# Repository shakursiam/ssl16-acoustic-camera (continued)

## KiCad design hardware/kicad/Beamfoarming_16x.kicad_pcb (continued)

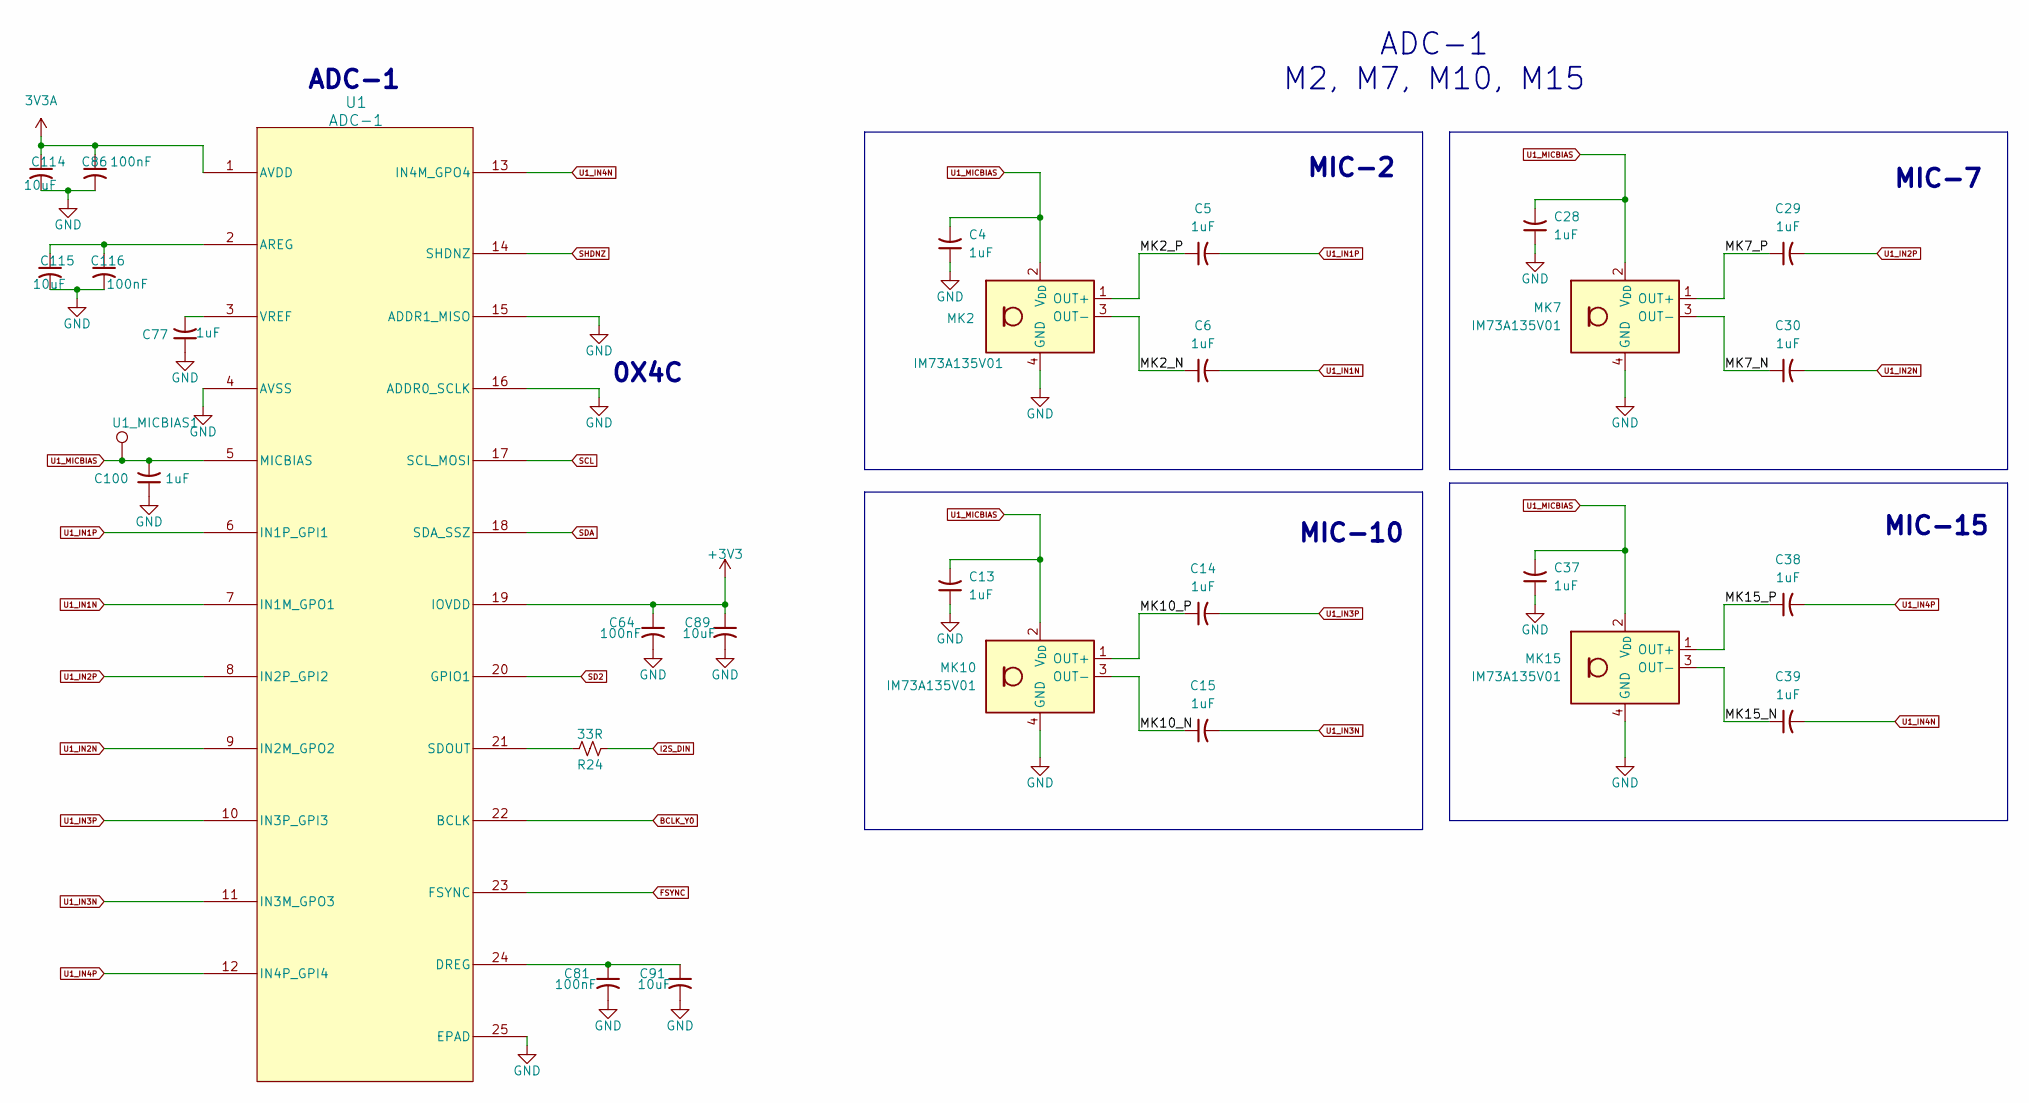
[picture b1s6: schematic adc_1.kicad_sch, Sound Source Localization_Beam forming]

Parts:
C4, C5, C6, C13, C14, C15, C28, C29, C30, C37, C38, C39, C77, C100: 1uF; C_0402_1005Metric
C64, C81, C86, C116: 100nF; C_0402_1005Metric
C89, C91, C114, C115: 10uF; C_0805_2012Metric_Pad1.18x1.45mm_HandSolder
MK2, MK7, MK10, MK15: IM73A135V01; Infineon_PG-LLGA-5-2
R24: 33R; R_0402_1005Metric
U1: ADC-1; RTW24_4P15X4P15_TEX
U1_MICBIAS1: TestPoint; TestPoint_Pad_D1.5mm

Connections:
3V3A: C86.1, C114.1, U1.1 (AVDD); also elsewhere on the board
+3V3: C64.1, C89.1, U1.19 (IOVDD); also elsewhere on the board
/ADC_1/MK2_N: C6.1, MK2.3 (OUT-)
/ADC_1/MK2_P: C5.1, MK2.1 (OUT+)
/ADC_1/MK7_N: C30.1, MK7.3 (OUT-)
/ADC_1/MK7_P: C29.1, MK7.1 (OUT+)
/ADC_1/MK10_N: C15.1, MK10.3 (OUT-)
/ADC_1/MK10_P: C14.1, MK10.1 (OUT+)
/ADC_1/MK15_N: C39.1, MK15.3 (OUT-)
/ADC_1/MK15_P: C38.1, MK15.1 (OUT+)
BCLK_Y0: U1.22 (BCLK); also elsewhere on the board
FSYNC: U1.23 (FSYNC); also elsewhere on the board
GND: C4.1, C13.1, C28.1, C37.1, C64.2, C77.1, C81.2, C86.2, C89.2, C91.2, C100.1, C114.2, C115.2, C116.2, MK2.4 (GND), MK2.5 (GND), MK7.4 (GND), MK7.5 (GND), MK10.4 (GND), MK10.5 (GND), MK15.4 (GND), MK15.5 (GND), U1.4 (AVSS), U1.15 (ADDR1_MISO), U1.16 (ADDR0_SCLK), U1.25 (EPAD); also elsewhere on the board
I2S_DIN: R24.1; also elsewhere on the board
unnamed: C115.1, C116.1, U1.2 (AREG)
unnamed: C81.1, C91.1, U1.24 (DREG)
unnamed: R24.2, U1.21 (SDOUT)
unnamed: C77.2, U1.3 (VREF)
SCL: U1.17 (SCL_MOSI); also elsewhere on the board
SD2: U1.20 (GPIO1); also elsewhere on the board
SDA: U1.18 (SDA_SSZ); also elsewhere on the board
SHDNZ: U1.14 (SHDNZ); also elsewhere on the board
U1_IN1N: C6.2, U1.7 (IN1M_GPO1)
U1_IN1P: C5.2, U1.6 (IN1P_GPI1)
U1_IN2N: C30.2, U1.9 (IN2M_GPO2)
U1_IN2P: C29.2, U1.8 (IN2P_GPI2)
U1_IN3N: C15.2, U1.11 (IN3M_GPO3)
U1_IN3P: C14.2, U1.10 (IN3P_GPI3)
U1_IN4N: C39.2, U1.13 (IN4M_GPO4)
U1_IN4P: C38.2, U1.12 (IN4P_GPI4)
U1_MICBIAS: C4.2, C13.2, C28.2, C37.2, C100.2, MK2.2 (V_{DD}), MK7.2 (V_{DD}), MK10.2 (V_{DD}), MK15.2 (V_{DD}), U1.5 (MICBIAS), U1_MICBIAS1.1 (1_1)

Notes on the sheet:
MIC-7
MIC-15
MIC-2
ADC-1
MIC-10
0X4C
ADC-1 M2, M7, M10, M15

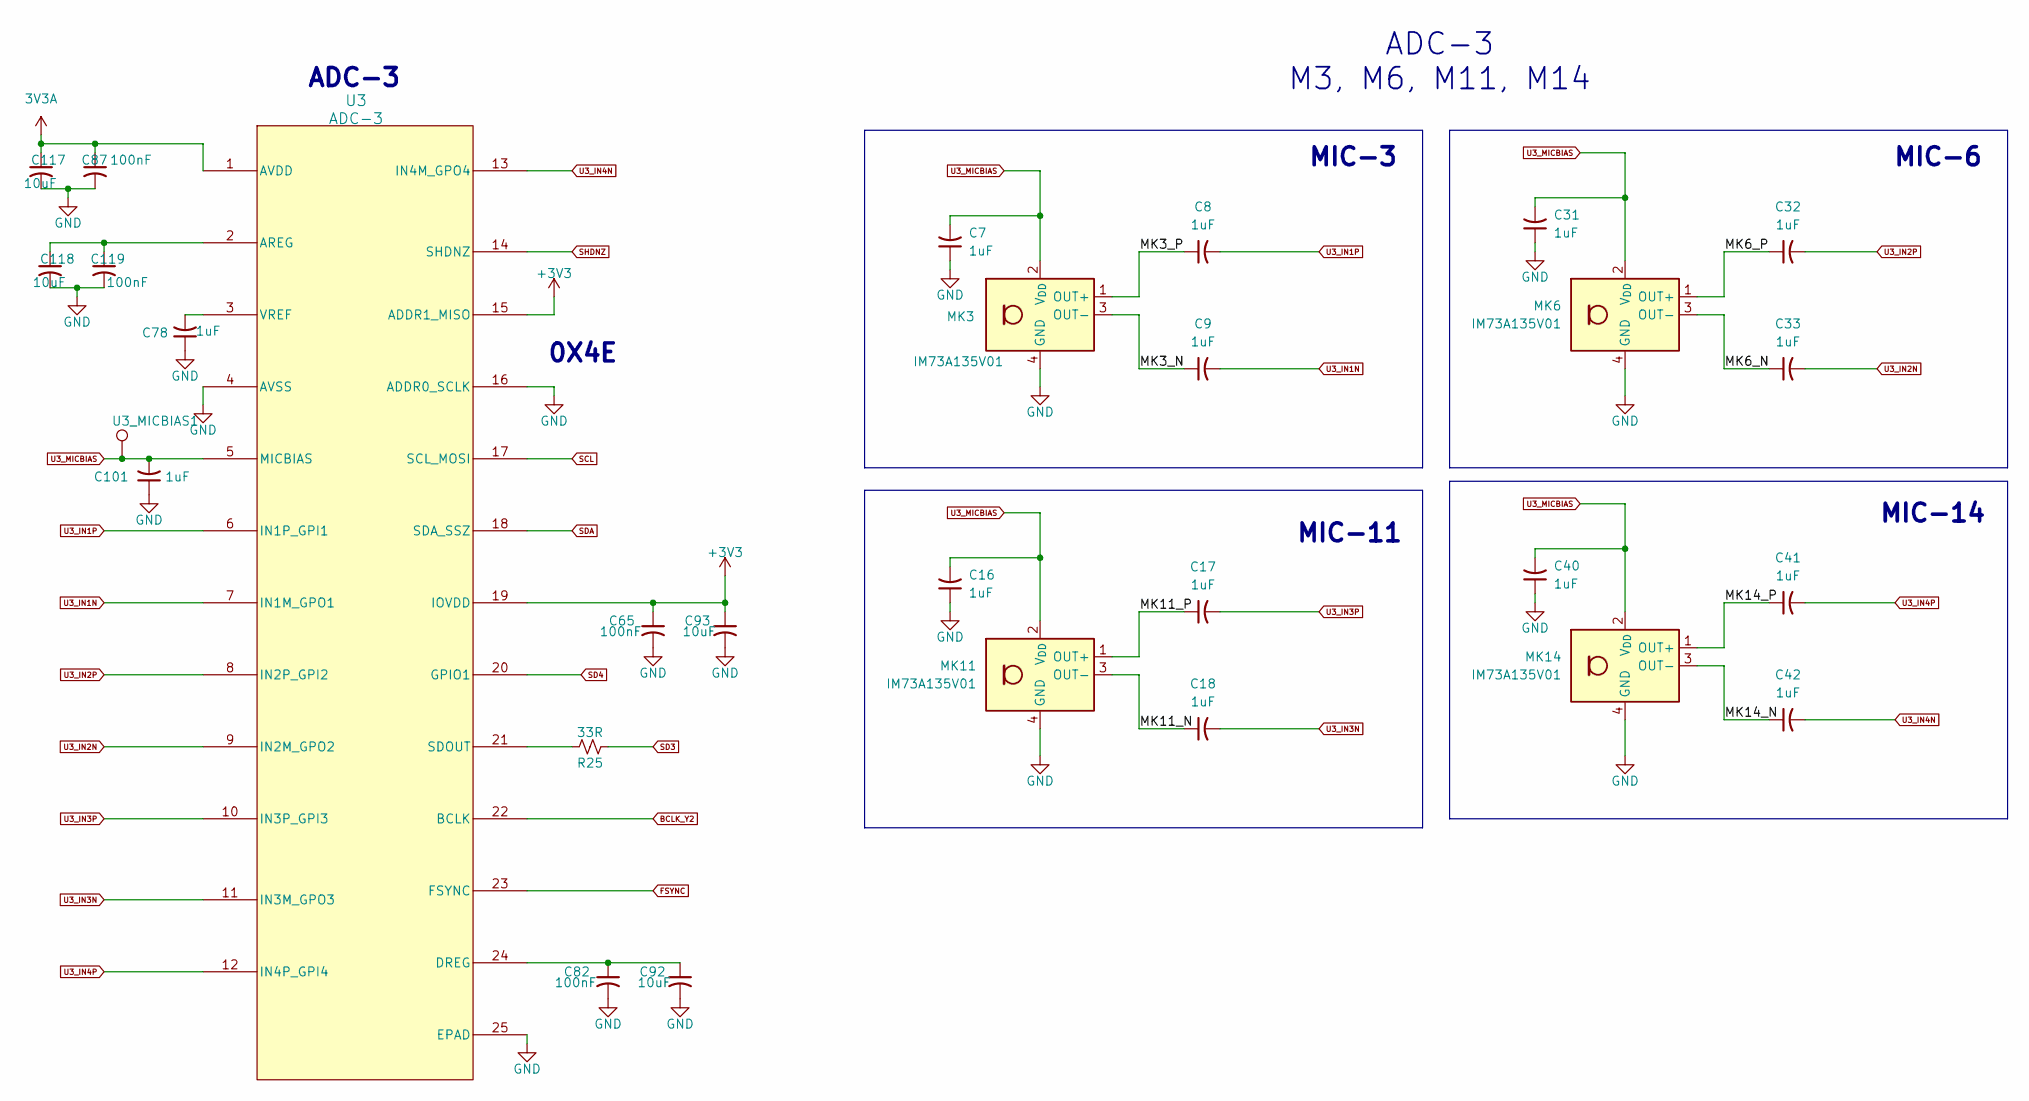
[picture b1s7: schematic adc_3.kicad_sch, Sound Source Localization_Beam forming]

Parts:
C7, C8, C9, C16, C17, C18, C31, C32, C33, C40, C41, C42, C78, C101: 1uF; C_0402_1005Metric
C65, C82, C87, C119: 100nF; C_0402_1005Metric
C92, C93, C117, C118: 10uF; C_0805_2012Metric_Pad1.18x1.45mm_HandSolder
MK3, MK6, MK11, MK14: IM73A135V01; Infineon_PG-LLGA-5-2
R25: 33R; R_0402_1005Metric
U3: ADC-3; RTW24_4P15X4P15_TEX
U3_MICBIAS1: TestPoint; TestPoint_Pad_D1.5mm

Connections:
3V3A: C87.1, C117.1, U3.1 (AVDD); also elsewhere on the board
+3V3: C65.1, C93.1, U3.15 (ADDR1_MISO), U3.19 (IOVDD); also elsewhere on the board
/ADC_3/MK3_N: C9.1, MK3.3 (OUT-)
/ADC_3/MK3_P: C8.1, MK3.1 (OUT+)
/ADC_3/MK6_N: C33.1, MK6.3 (OUT-)
/ADC_3/MK6_P: C32.1, MK6.1 (OUT+)
/ADC_3/MK11_N: C18.1, MK11.3 (OUT-)
/ADC_3/MK11_P: C17.1, MK11.1 (OUT+)
/ADC_3/MK14_N: C42.1, MK14.3 (OUT-)
/ADC_3/MK14_P: C41.1, MK14.1 (OUT+)
BCLK_Y2: U3.22 (BCLK); also elsewhere on the board
FSYNC: U3.23 (FSYNC); also elsewhere on the board
GND: C7.1, C16.1, C31.1, C40.1, C65.2, C78.1, C82.2, C87.2, C92.2, C93.2, C101.1, C117.2, C118.2, C119.2, MK3.4 (GND), MK3.5 (GND), MK6.4 (GND), MK6.5 (GND), MK11.4 (GND), MK11.5 (GND), MK14.4 (GND), MK14.5 (GND), U3.4 (AVSS), U3.16 (ADDR0_SCLK), U3.25 (EPAD); also elsewhere on the board
unnamed: C118.1, C119.1, U3.2 (AREG)
unnamed: C82.1, C92.1, U3.24 (DREG)
unnamed: R25.2, U3.21 (SDOUT)
unnamed: C78.2, U3.3 (VREF)
SCL: U3.17 (SCL_MOSI); also elsewhere on the board
SD3: R25.1; also elsewhere on the board
SD4: U3.20 (GPIO1); also elsewhere on the board
SDA: U3.18 (SDA_SSZ); also elsewhere on the board
SHDNZ: U3.14 (SHDNZ); also elsewhere on the board
U3_IN1N: C9.2, U3.7 (IN1M_GPO1)
U3_IN1P: C8.2, U3.6 (IN1P_GPI1)
U3_IN2N: C33.2, U3.9 (IN2M_GPO2)
U3_IN2P: C32.2, U3.8 (IN2P_GPI2)
U3_IN3N: C18.2, U3.11 (IN3M_GPO3)
U3_IN3P: C17.2, U3.10 (IN3P_GPI3)
U3_IN4N: C42.2, U3.13 (IN4M_GPO4)
U3_IN4P: C41.2, U3.12 (IN4P_GPI4)
U3_MICBIAS: C7.2, C16.2, C31.2, C40.2, C101.2, MK3.2 (V_{DD}), MK6.2 (V_{DD}), MK11.2 (V_{DD}), MK14.2 (V_{DD}), U3.5 (MICBIAS), U3_MICBIAS1.1 (1_1)

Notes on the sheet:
MIC-6
ADC-3 M3, M6, M11, M14
0X4E
MIC-14
ADC-3
MIC-3
MIC-11

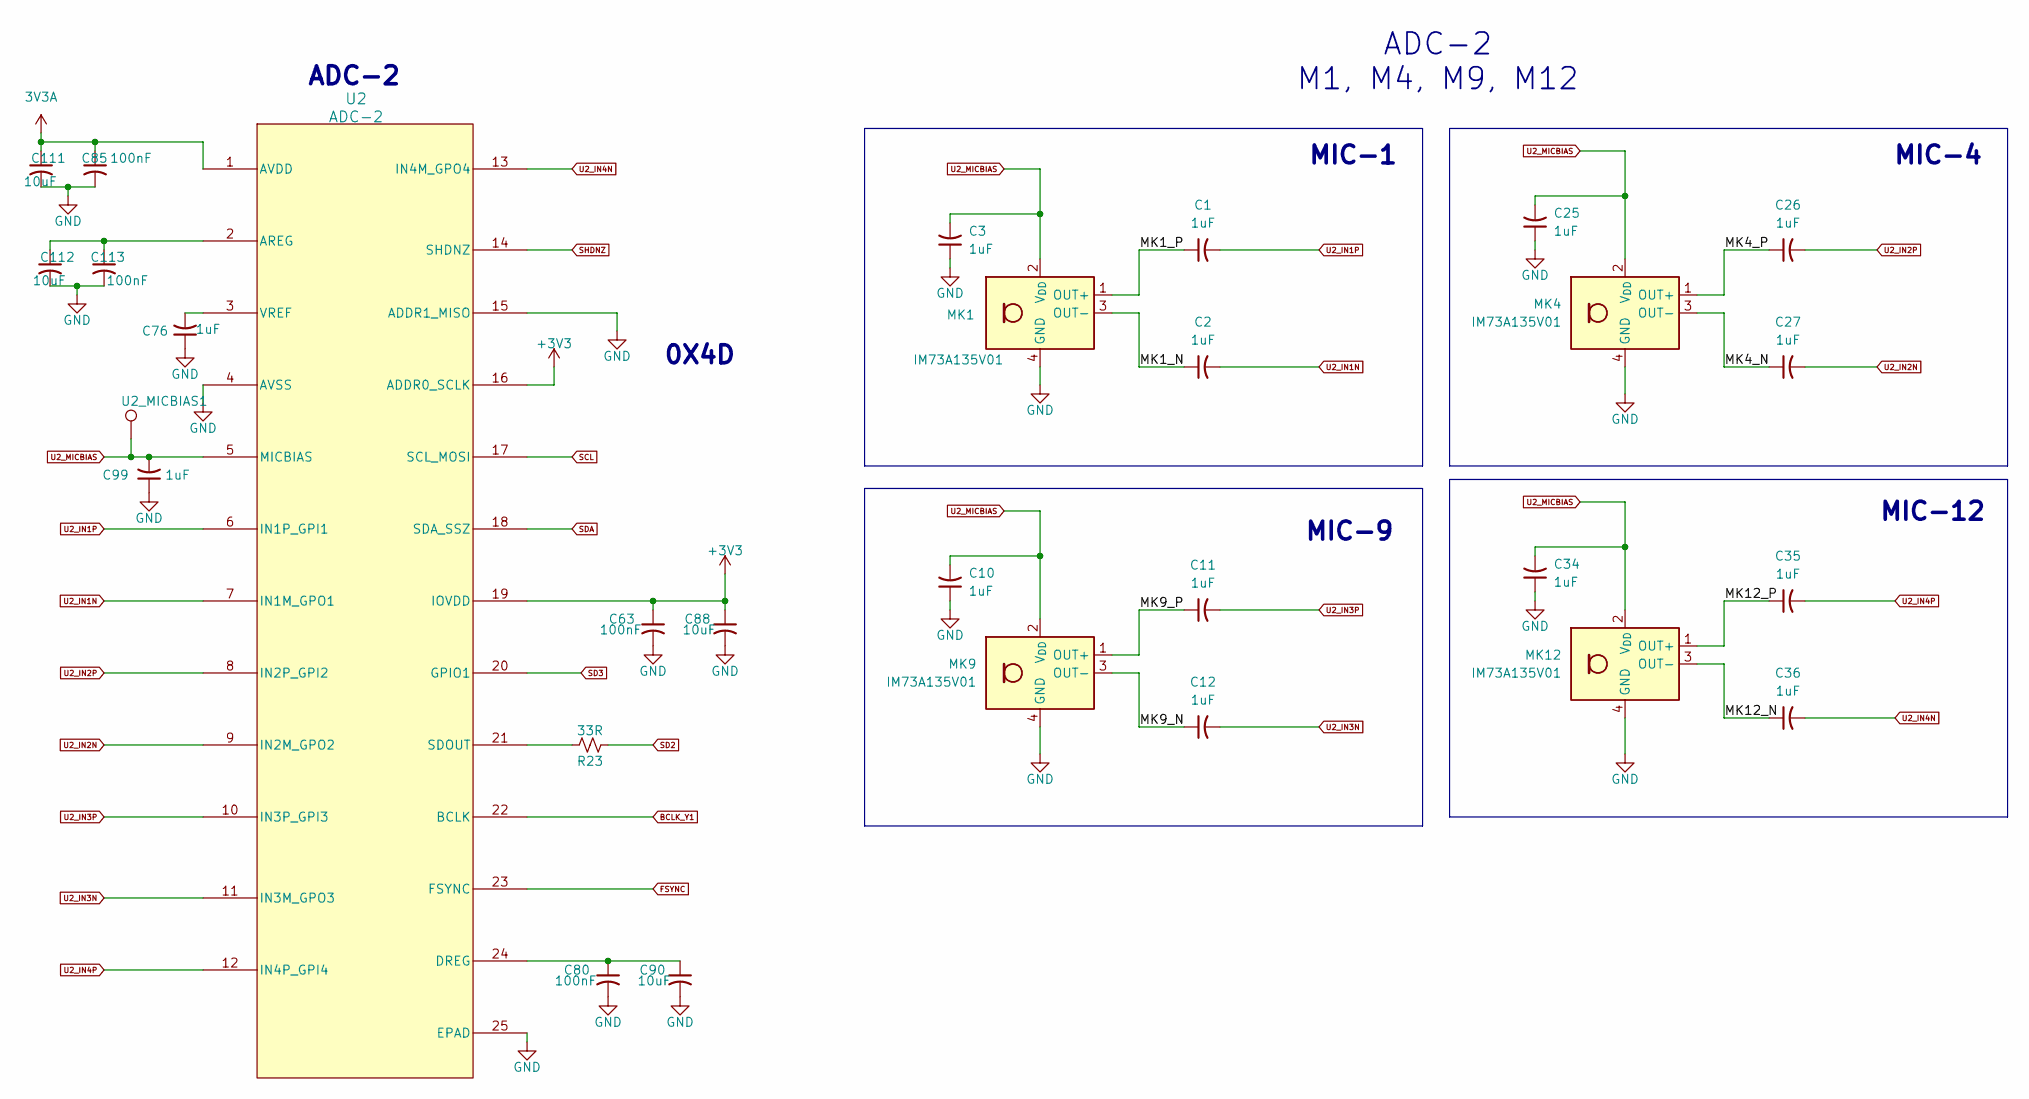
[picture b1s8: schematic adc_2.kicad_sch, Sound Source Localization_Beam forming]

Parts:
C1, C2, C3, C10, C11, C12, C25, C26, C27, C34, C35, C36, C76, C99: 1uF; C_0402_1005Metric
C63, C80, C85, C113: 100nF; C_0402_1005Metric
C88, C90, C111, C112: 10uF; C_0805_2012Metric_Pad1.18x1.45mm_HandSolder
MK1, MK4, MK9, MK12: IM73A135V01; Infineon_PG-LLGA-5-2
R23: 33R; R_0402_1005Metric
U2: ADC-2; RTW24_4P15X4P15_TEX
U2_MICBIAS1: TestPoint; TestPoint_Pad_D1.5mm

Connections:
3V3A: C85.1, C111.1, U2.1 (AVDD); also elsewhere on the board
+3V3: C63.1, C88.1, U2.16 (ADDR0_SCLK), U2.19 (IOVDD); also elsewhere on the board
/ADC_2/MK1_N: C2.1, MK1.3 (OUT-)
/ADC_2/MK1_P: C1.1, MK1.1 (OUT+)
/ADC_2/MK4_N: C27.1, MK4.3 (OUT-)
/ADC_2/MK4_P: C26.1, MK4.1 (OUT+)
/ADC_2/MK9_N: C12.1, MK9.3 (OUT-)
/ADC_2/MK9_P: C11.1, MK9.1 (OUT+)
/ADC_2/MK12_N: C36.1, MK12.3 (OUT-)
/ADC_2/MK12_P: C35.1, MK12.1 (OUT+)
BCLK_Y1: U2.22 (BCLK); also elsewhere on the board
FSYNC: U2.23 (FSYNC); also elsewhere on the board
GND: C3.1, C10.1, C25.1, C34.1, C63.2, C76.1, C80.2, C85.2, C88.2, C90.2, C99.1, C111.2, C112.2, C113.2, MK1.4 (GND), MK1.5 (GND), MK4.4 (GND), MK4.5 (GND), MK9.4 (GND), MK9.5 (GND), MK12.4 (GND), MK12.5 (GND), U2.4 (AVSS), U2.15 (ADDR1_MISO), U2.25 (EPAD); also elsewhere on the board
unnamed: C112.1, C113.1, U2.2 (AREG)
unnamed: C80.1, C90.1, U2.24 (DREG)
unnamed: R23.2, U2.21 (SDOUT)
unnamed: C76.2, U2.3 (VREF)
SCL: U2.17 (SCL_MOSI); also elsewhere on the board
SD2: R23.1; also elsewhere on the board
SD3: U2.20 (GPIO1); also elsewhere on the board
SDA: U2.18 (SDA_SSZ); also elsewhere on the board
SHDNZ: U2.14 (SHDNZ); also elsewhere on the board
U2_IN1N: C2.2, U2.7 (IN1M_GPO1)
U2_IN1P: C1.2, U2.6 (IN1P_GPI1)
U2_IN2N: C27.2, U2.9 (IN2M_GPO2)
U2_IN2P: C26.2, U2.8 (IN2P_GPI2)
U2_IN3N: C12.2, U2.11 (IN3M_GPO3)
U2_IN3P: C11.2, U2.10 (IN3P_GPI3)
U2_IN4N: C36.2, U2.13 (IN4M_GPO4)
U2_IN4P: C35.2, U2.12 (IN4P_GPI4)
U2_MICBIAS: C3.2, C10.2, C25.2, C34.2, C99.2, MK1.2 (V_{DD}), MK4.2 (V_{DD}), MK9.2 (V_{DD}), MK12.2 (V_{DD}), U2.5 (MICBIAS), U2_MICBIAS1.1 (1_1)

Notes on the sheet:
0X4D
MIC-1
MIC-4
ADC-2
ADC-2 M1, M4, M9, M12
MIC-12
MIC-9

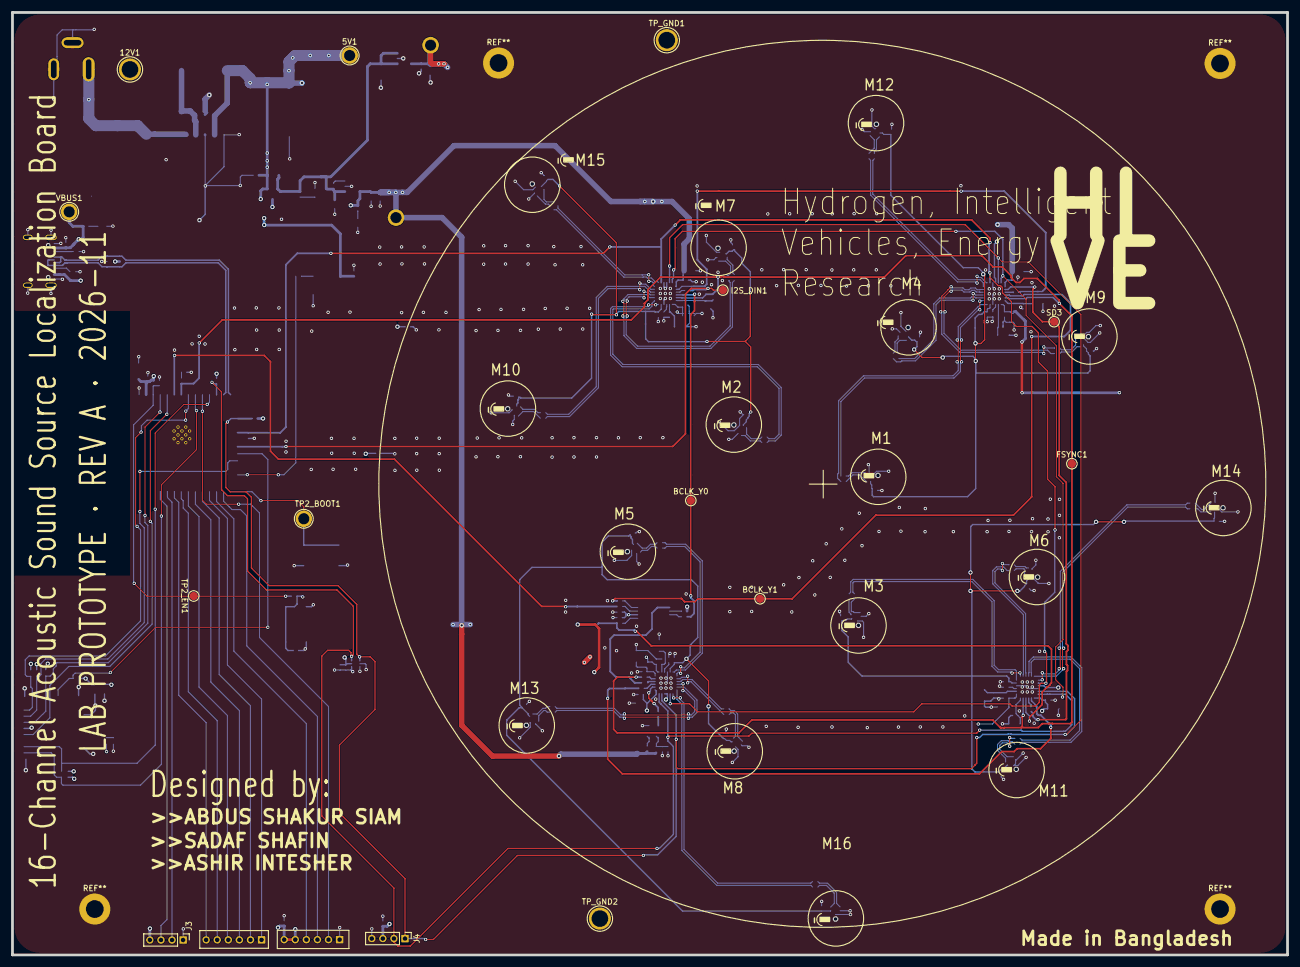
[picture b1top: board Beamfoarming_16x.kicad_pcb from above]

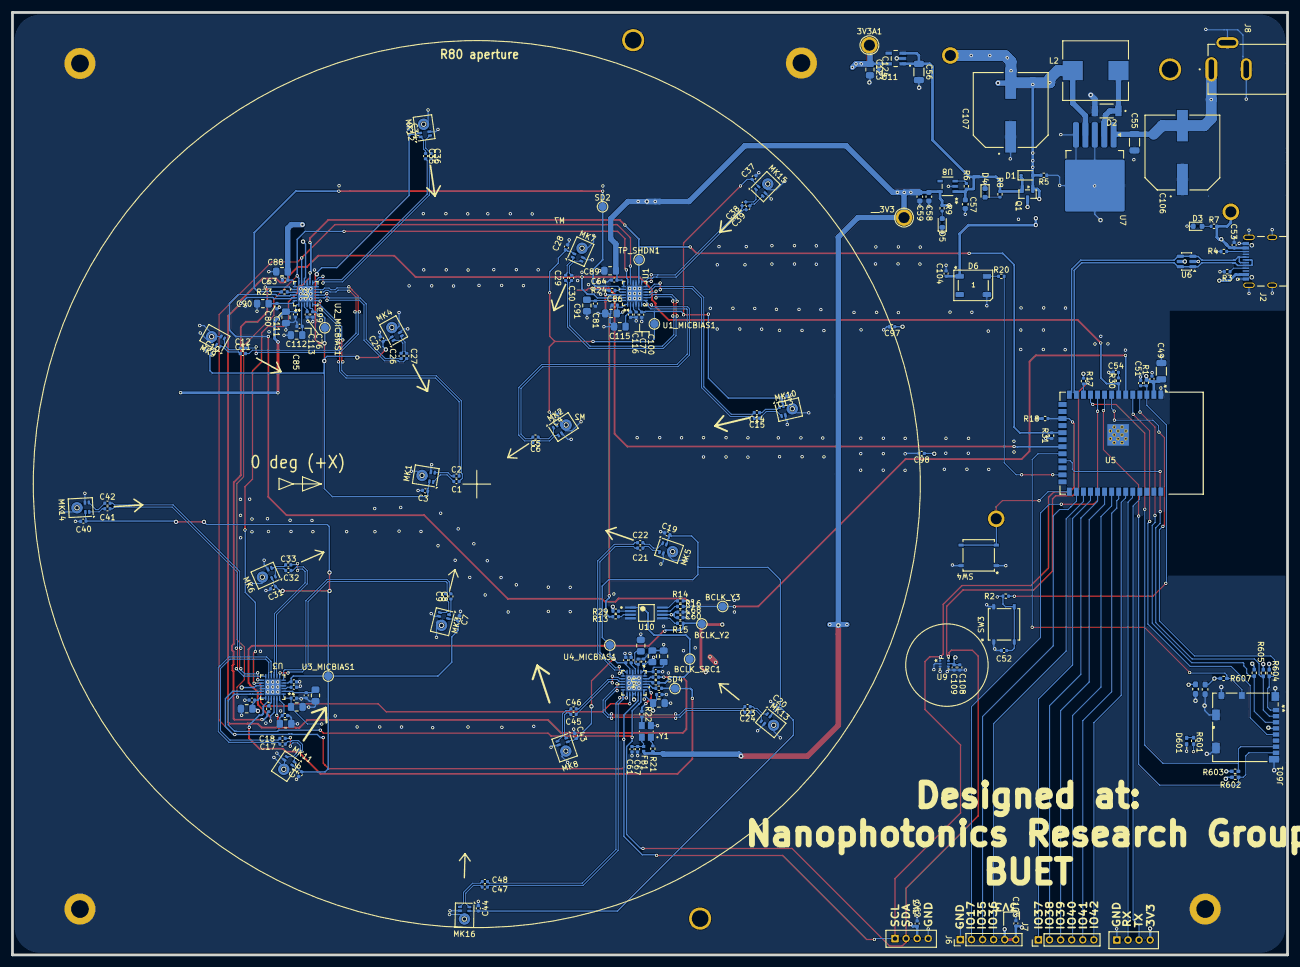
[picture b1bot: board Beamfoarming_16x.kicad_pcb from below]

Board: 4 copper layers, 230.0 x 170.0 mm, 221 parts (207 on the bottom side), 149 nets.

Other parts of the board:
__3V3: TestPoint_Plated_Hole_D2.0mm

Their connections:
+3V3: __3V3.1 (1_1); also elsewhere on the board
